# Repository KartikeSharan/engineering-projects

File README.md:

# Engineering Projects: Kartike Sharan

Hardware and software projects from my BEng in Electronics & Electrical Engineering at the University of Glasgow (including an exchange semester at UESTC, Chengdu), my drone society and a drone start-up. Each folder has its own README saying what I did.

## PCB design

| Project | Summary |
|---|---|
| [`atreides-flight-controller`](atreides-flight-controller/) | 6-layer drone flight controller for a start-up; I owned the PCB layout (KiCad) |
| [`gud-drone-devkit`](gud-drone-devkit/) | Solder-free educational drone kit for schools outreach; my electronics design (ESP32-C3, KiCad) |
| [`gud-flight-controller`](gud-flight-controller/) | Society flight controller schematic modelled on the Pixhawk 6 standard (KiCad) |
| [`year1-pcb-design`](year1-pcb-design/) | Electronic dice and logic boards, designed, built and tested (OrCAD, Allegro) |
| [`dp2-orcad-allegro-lab1`](dp2-orcad-allegro-lab1/) | Op-amp board schematic and layout (OrCAD, Allegro) |

## Digital design and HDL

| Project | Summary |
|---|---|
| [`risc16-cpu`](risc16-cpu/) | 16-bit RISC CPU in Verilog, with a review of the submitted design and a revised version with a self-checking testbench run by GitHub Actions |
| [`de2-vhdl-ring-counter`](de2-vhdl-ring-counter/) | Ring counter on a MAX 10 FPGA (Quartus) |
| [`quine-mccluskey`](quine-mccluskey/) | Quine–McCluskey Boolean minimiser in Python with don't-care support |

## Embedded systems

| Project | Summary |
|---|---|
| [`tdp3-line-following-robot`](tdp3-line-following-robot/) | Team robot I lead: register-level C on an Arm Cortex-M0+ with a Python build and flash tool |
| [`stm32-embedded`](stm32-embedded/) | STM32 labs and a cold-chain transport logger (TMP102 over I2C, ADXL345 over SPI) |
| [`rtcs-arm-cortex-m4-labs`](rtcs-arm-cortex-m4-labs/) | Arm Thumb assembly, interrupts and timers on an STM32F407 |

## Analogue, devices and signals

| Project | Summary |
|---|---|
| [`comms-signal-processing-python`](comms-signal-processing-python/) | Sampling, AM and a DFT checked against the FFT, in Python |
| [`tcad-pn-junction`](tcad-pn-junction/) | Silicon p-n junction simulated in Synopsys Sentaurus TCAD |
| [`year1-analogue-labs`](year1-analogue-labs/) | PSpice DC analysis and RC filter labs |

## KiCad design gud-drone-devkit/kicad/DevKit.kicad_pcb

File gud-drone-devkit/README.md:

# Educational drone kit (Glasgow University Drones)

A solder-free, modular drone kit for the society's outreach with secondary schools: pupils assemble and programme it themselves, with JST connectors on the battery and motors and USB-C for power and programming. I proposed the kit and designed its electronics as Head of Electronics.

| | |
|---|---|
| Board | 2-layer, 70.6 x 70.6 mm |
| Main parts | ESP32-C3 module, ICM-42670-P IMU, two DRV8833 dual H-bridges (four motors), TPS63001 buck-boost, BQ24074 charger |
| Power | Buck-boost holds the 3.3 V rail across the LiPo's full range; diode-OR path from USB or battery with reverse-polarity protection |
| Status | ERC/DRC clean, first boards fabricated, not yet assembled |

## Folders

| Folder | Contents |
|---|---|
| `kicad/` | KiCad project, schematic, layout and the custom IMU and connector libraries |
| `manufacturing/` | Gerbers, drill files, BOM and pick-and-place |
| `docs/` | Schematic PDF and the chassis engineering drawing |

The chassis drawing is the mechanical team's; I coordinated PCB size and component positions, including the battery, with them.

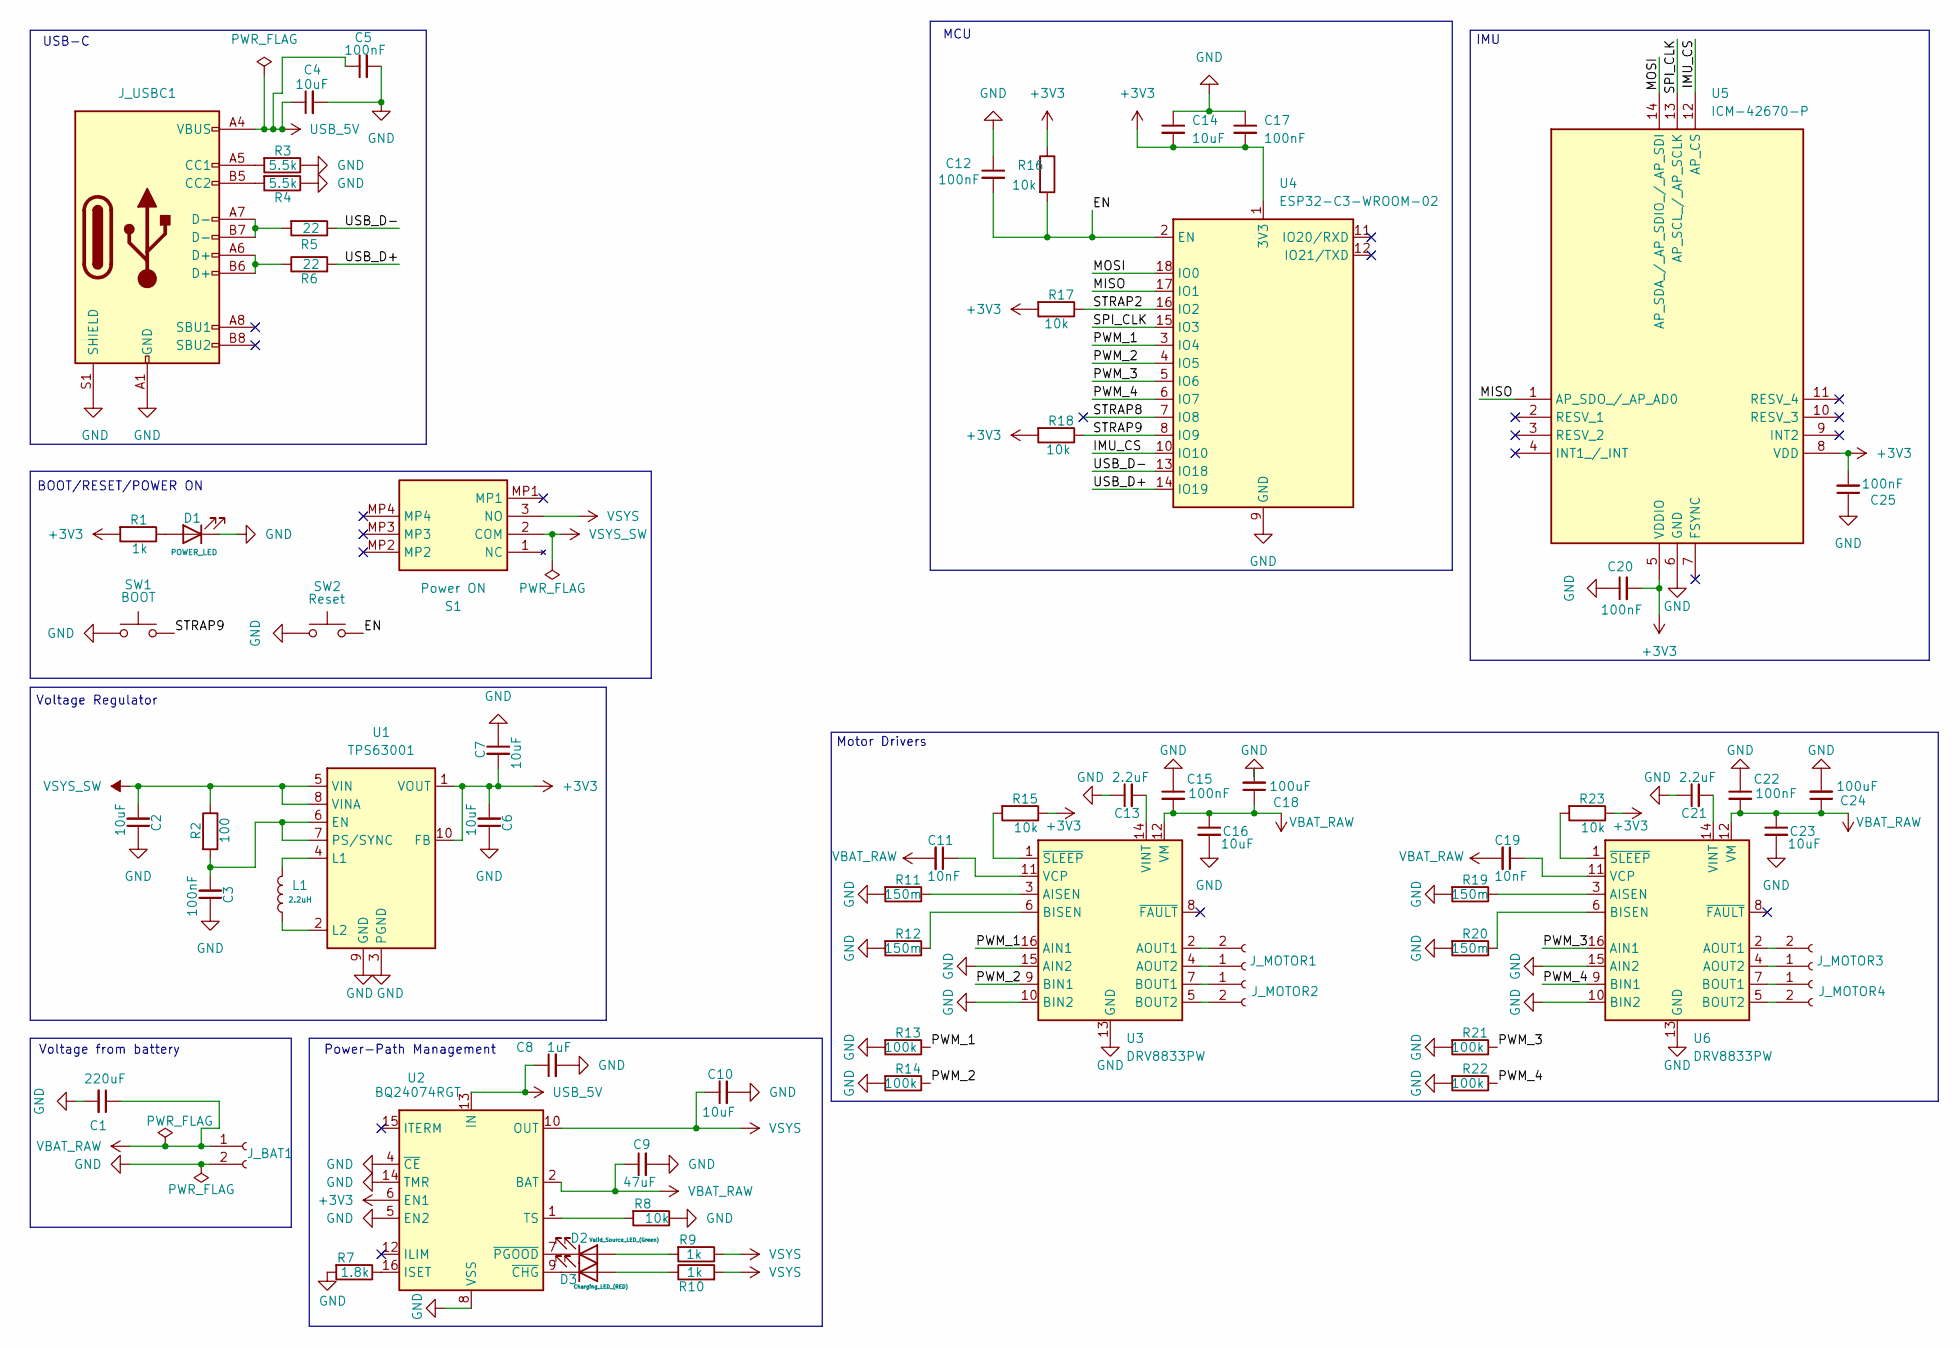
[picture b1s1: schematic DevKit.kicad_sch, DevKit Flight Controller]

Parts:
C1: 220uF; CP_Elec_6.3x5.4
C2, C4, C6, C7, C10, C14, C16, C23: 10uF; C_1206_3216Metric
C3, C5, C12, C15, C17, C20, C22, C25: 100nF; C_0603_1608Metric
C8: 1uF; C_1206_3216Metric
C9: 47uF; C_1206_3216Metric
C11, C19: 10nF; C_0603_1608Metric
C13, C21: 2.2uF; C_0805_2012Metric
C18, C24: 100uF; CP_Elec_6.3x5.4
D1: POWER_LED; LED_0805_2012Metric
D2: Valid_Source_LED_(Green); LED_0805_2012Metric
D3: Charging_LED_(RED); LED_0805_2012Metric
J_BAT1: JST_PH_B2B-PH-K_1x02_P2.00mm_Vertical
J_MOTOR1, J_MOTOR2, J_MOTOR3, J_MOTOR4: JST_GH_BM02B-GHS-TBT_1x02-1MP_P1.25mm_Vertical
J_USBC1: USB_C_Receptacle_GCT_USB4105-xx-A_16P_TopMnt_Horizontal
L1: 2.2uH; L_0805_2012Metric
R1, R9, R10: 1k; R_0603_1608Metric
R2: 100; R_0603_1608Metric
R3, R4: 5.5k; R_0603_1608Metric
R5, R6: 22; R_0603_1608Metric
R7: 1.8k; R_0603_1608Metric
R8, R15, R16, R17, R18, R23: 10k; R_0603_1608Metric
R11, R12, R19, R20: 150m; R_0603_1608Metric
R13, R14, R21, R22: 100k; R_0603_1608Metric
S1: Power ON; PCM12SMTBR; Mouser Part Number 611-PCM12SMTBR
SW1: BOOT; SW_Push_1P1T_NO_CK_KMR2
SW2: Reset; SW_Push_1P1T_NO_CK_KMR2
U1: TPS63001; Texas_DRC0010J_ThermalVias
U2: BQ24074RGT; VQFN-16-1EP_3x3mm_P0.5mm_EP1.6x1.6mm
U3, U6: DRV8833PW; TSSOP-16_4.4x5mm_P0.65mm
U4: ESP32-C3-WROOM-02
U5: ICM-42670-P; ICM42670P; Manufacturer_Part_Number ICM-42670-P; Mouser Part Number 410-ICM-42670-P

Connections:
+3V3: C6.2, C7.2, C14.2, C17.2, C20.2, C25.2, R1.2, R15.1, R16.1, R17.2, R18.2, R23.1, U1.1 (VOUT), U1.10 (FB), U2.6 (EN1), U4.1 (3V3), U5.5 (VDDIO), U5.8 (VDD)
/EN: C12.2, R16.2, SW2.2, U4.2 (EN)
/IMU_CS: U4.10 (IO10), U5.12 (AP_CS)
/MISO: U4.17 (IO1), U5.1 (AP_SDO_/_AP_AD0)
/MOSI: U4.18 (IO0), U5.14 (AP_SDA_/_AP_SDIO_/_AP_SDI)
/PWM_1: R13.1, U3.16 (AIN1), U4.3 (IO4)
/PWM_2: R14.1, U3.9 (BIN1), U4.4 (IO5)
/PWM_3: R21.1, U4.5 (IO6), U6.16 (AIN1)
/PWM_4: R22.1, U4.6 (IO7), U6.9 (BIN1)
/SPI_CLK: U4.15 (IO3), U5.13 (AP_SCL_/_AP_SCLK)
/STRAP2: R17.1, U4.16 (IO2)
/STRAP8: U4.7 (IO8)
/STRAP9: R18.1, SW1.2, U4.8 (IO9)
/USB_D+: R6.2, U4.14 (IO19)
/USB_D-: R5.1, U4.13 (IO18)
GND: C1.2, C2.1, C3.1, C4.2, C5.2, C6.1, C7.1, C8.2, C9.2, C10.2, C12.1, C13.1, C14.1, C15.1, C16.2, C17.1, C18.2, C20.1, C21.1, C22.1, C23.2, C24.2, C25.1, D1.1 (K), J_BAT1.2, J_USBC1.A1 (GND), J_USBC1.A12 (GND), J_USBC1.B1 (GND), J_USBC1.B12 (GND), J_USBC1.S1 (SHIELD), R3.1, R4.1, R7.2, R8.1, R11.2, R12.2, R13.2, R14.2, R19.2, R20.2, R21.2, R22.2, SW1.1, SW2.1, U1.3 (PGND), U1.9 (GND), U1.11 (PGND), U2.4 (~CE), U2.5 (EN2), U2.8 (VSS), U2.14 (TMR), U2.17 (VSS), U3.10 (BIN2), U3.13 (GND), U3.15 (AIN2), U4.9 (GND), U4.19 (GND), U5.6 (GND), U6.10 (BIN2), U6.13 (GND), U6.15 (AIN2)
unnamed: D1.2 (A), R1.1
unnamed: D2.2 (A), R9.2
unnamed: D2.1 (K), U2.7 (~PGOOD)
unnamed: D3.2 (A), R10.1
unnamed: D3.1 (K), U2.9 (~CHG)
unnamed: J_MOTOR1.1, U3.4 (AOUT2)
unnamed: J_MOTOR1.2, U3.2 (AOUT1)
unnamed: J_MOTOR2.1, U3.7 (BOUT1)
unnamed: J_MOTOR2.2, U3.5 (BOUT2)
unnamed: J_MOTOR3.1, U6.4 (AOUT2)
unnamed: J_MOTOR3.2, U6.2 (AOUT1)
unnamed: J_MOTOR4.1, U6.7 (BOUT1)
unnamed: J_MOTOR4.2, U6.5 (BOUT2)
unnamed: J_USBC1.A5 (CC1), R3.2
unnamed: J_USBC1.B5 (CC2), R4.2
unnamed: J_USBC1.A6 (D+), J_USBC1.B6 (D+), R6.1
unnamed: J_USBC1.A7 (D-), J_USBC1.B7 (D-), R5.2
unnamed: C3.2, R2.2, U1.6 (EN), U1.7 (PS/SYNC)
unnamed: L1.2, U1.4 (L1)
unnamed: L1.1, U1.2 (L2)
unnamed: R7.1, U2.16 (ISET)
unnamed: R8.2, U2.1 (TS)
unnamed: R11.1, U3.3 (AISEN)
unnamed: R12.1, U3.6 (BISEN)
unnamed: C11.1, U3.11 (VCP)
unnamed: C13.2, U3.14 (VINT)
unnamed: R15.2, U3.1 (~SLEEP)
unnamed: R19.1, U6.3 (AISEN)
unnamed: R20.1, U6.6 (BISEN)
unnamed: C19.1, U6.11 (VCP)
unnamed: C21.2, U6.14 (VINT)
unnamed: R23.2, U6.1 (~SLEEP)
USB_5V: C4.1, C5.1, C8.1, J_USBC1.A4 (VBUS), J_USBC1.A9 (VBUS), J_USBC1.B4 (VBUS), J_USBC1.B9 (VBUS), U2.13 (IN)
VBAT_RAW: C1.1, C9.1, C11.2, C15.2, C16.1, C18.1, C19.2, C22.2, C23.1, C24.1, J_BAT1.1, U2.2 (BAT), U2.3 (BAT), U3.12 (VM), U6.12 (VM)
VSYS: C10.1, R9.1, R10.2, S1.3 (NO), U2.10 (OUT), U2.11 (OUT)
VSYS_SW: C2.2, R2.1, S1.2 (COM), U1.5 (VIN), U1.8 (VINA)

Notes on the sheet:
MCU
Voltage Regulator
BOOT/RESET/POWER ON
Voltage from battery
USB-C
Power-Path Management
Motor Drivers
IMU

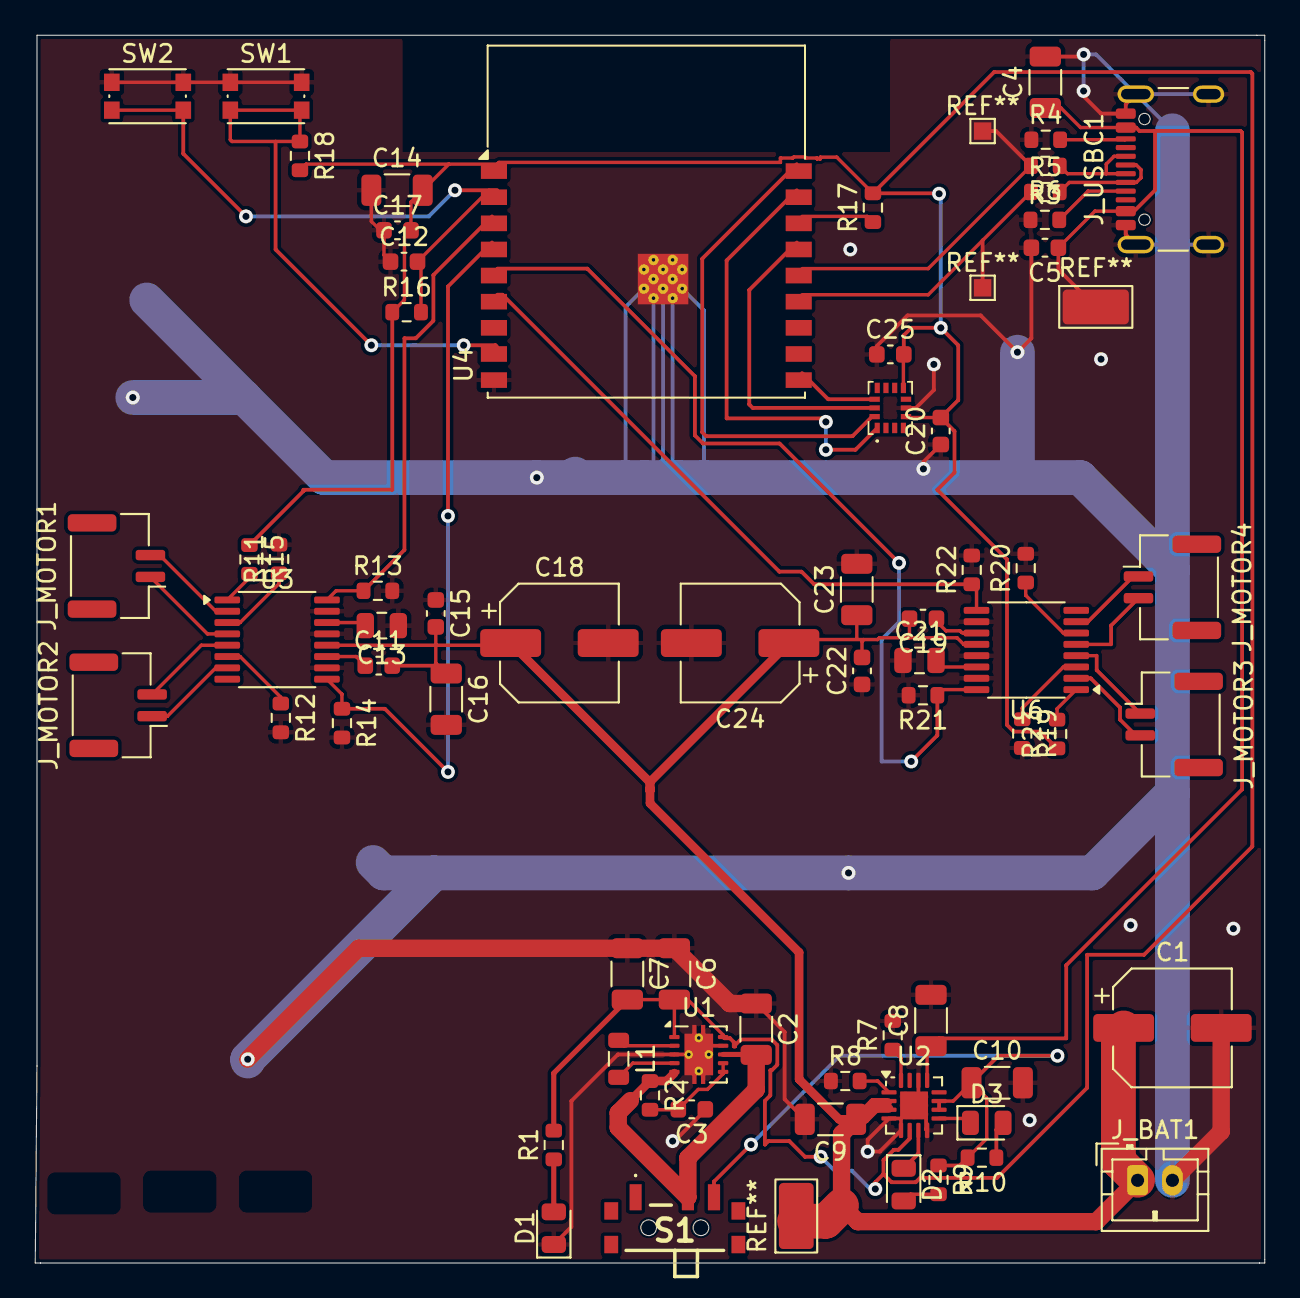
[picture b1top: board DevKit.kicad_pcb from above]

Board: 2 copper layers, 70.6 x 70.5 mm, 67 parts (0 on the bottom side), 51 nets.

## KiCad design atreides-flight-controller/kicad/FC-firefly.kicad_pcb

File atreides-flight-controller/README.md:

# FC-Firefly: drone flight controller PCB (Atreides Industries)

Flight controller board for an early-stage drone start-up, where I worked as a voluntary electronic engineer (Jun to Nov 2025). Added now that the NDA no longer applies.

| | |
|---|---|
| Board | 6-layer, impedance-controlled, 59.6 x 66.6 mm, 2.17 mm thick |
| Parts | 25 BOM lines, 43 placements on the top side |
| Tools | KiCad (schematic, layout, ERC/DRC, Gerber and assembly outputs) |

## My role

I owned the **PCB layout**, working alongside the schematic engineer, who designed the circuit. I checked every footprint against the manufacturers' drawings, cleared ERC and DRC, kept the board's interfaces compatible with the mechanical and electronics engineers, and delivered the manufacture-ready files in `manufacturing/`.

## Folders

| Folder | Contents |
|---|---|
| `kicad/` | KiCad project, schematic and layout, plus the Bosch BMI323 (IMU) and BMM350 (magnetometer) symbol and footprint libraries |
| `manufacturing/gerbers/` | Gerbers, drill files and drill maps as sent to fabrication |
| `manufacturing/assembly/` | BOM and pick-and-place files |

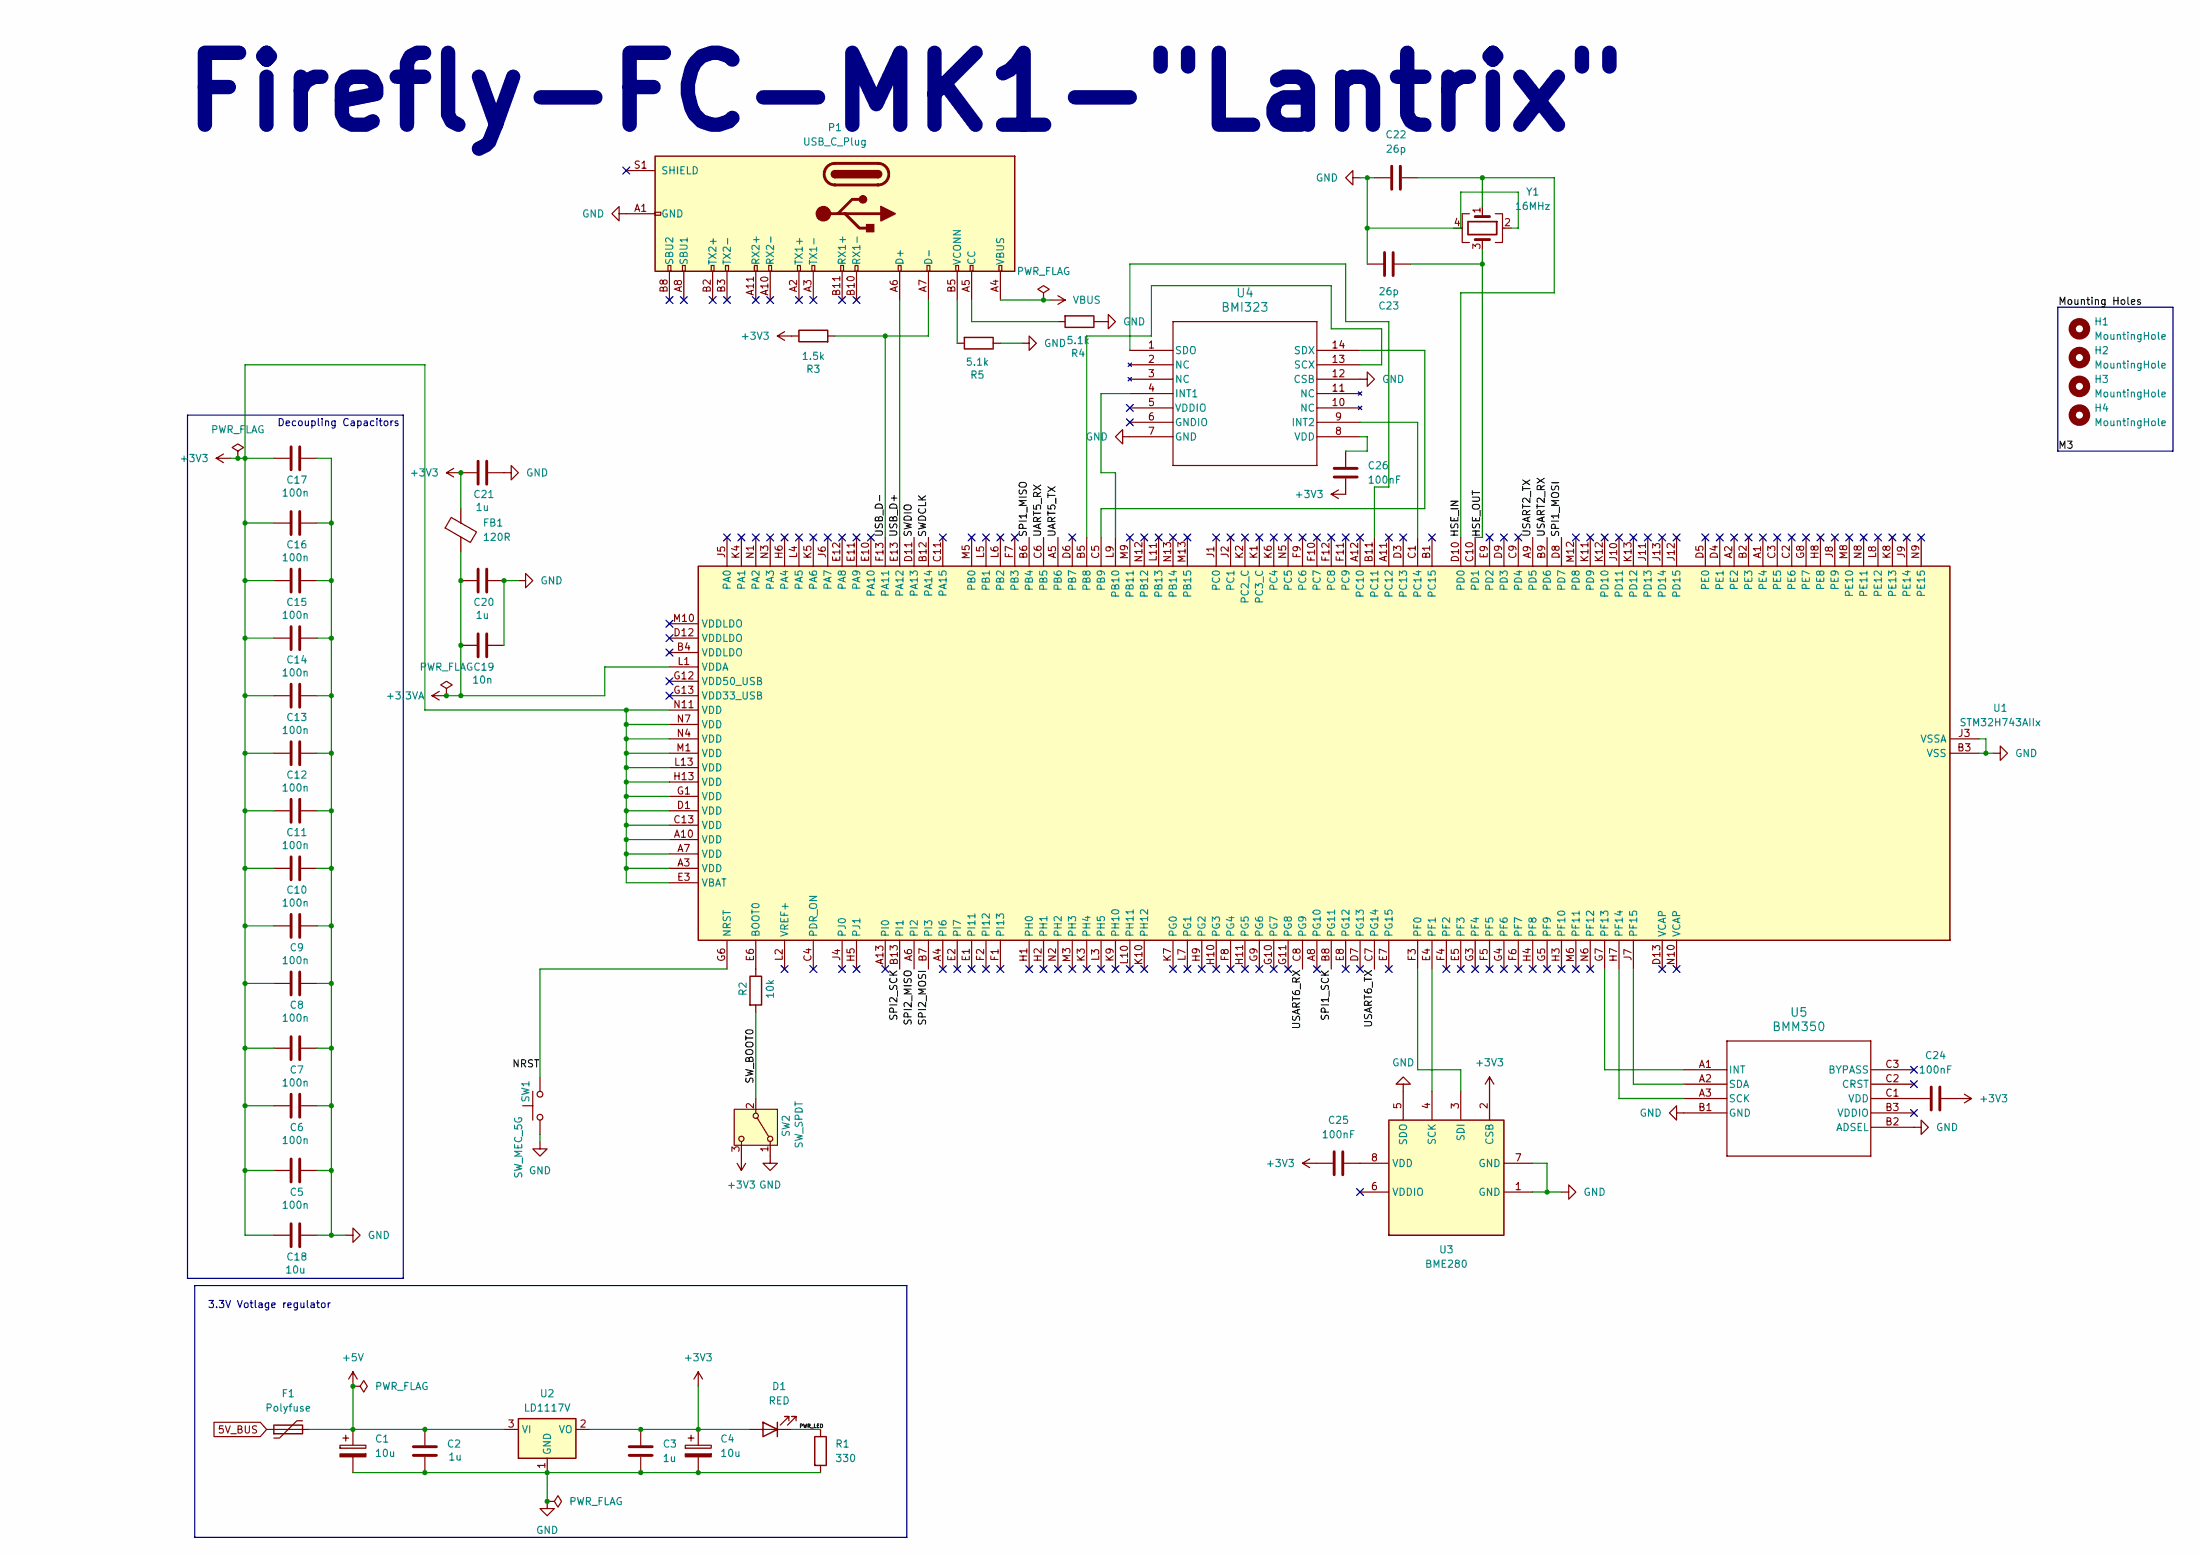
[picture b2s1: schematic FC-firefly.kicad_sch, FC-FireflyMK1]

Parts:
C1, C4: 10u; CP_Elec_3x5.3
C2, C3, C20: 1u; C_0805_2012Metric
C5, C6, C7, C8, C9, C10, C11, C12, C13, C14, C15, C16, C17: 100n; C_0805_2012Metric
C18: 10u; C_0805_2012Metric
C19: 10n; CP_Elec_3x5.3
C21: 1u; CP_Elec_3x5.3
C22, C23: 26p; C_0805_2012Metric
C24, C25, C26: 100nF; C_0805_2012Metric
D1: RED; LED_D5.0mm
F1: Polyfuse; Fuse_1812_4532Metric
FB1: 120R; L_0805_2012Metric
H1, H2, H3, H4: MountingHole; MountingHole_3.2mm_M3
P1: USB_C_Plug; USB_C_Receptacle_HRO_TYPE-C-31-M-12
R1: 330; R_0201_0603Metric_Pad0.64x0.40mm_HandSolder
R2: 10k; R_0201_0603Metric_Pad0.64x0.40mm_HandSolder
R3: 1.5k; R_0201_0603Metric_Pad0.64x0.40mm_HandSolder
R4, R5: 5.1k; R_0201_0603Metric_Pad0.64x0.40mm_HandSolder
SW1: SW_MEC_5G; SW_MEC_5GSH9
SW2: SW_SPDT; SW_SPDT_PCM12
U1: STM32H743AIIx; UFBGA-169_7x7mm_Layout13x13_P0.5mm
U2: LD1117V; TO-220-3_Vertical
U3: BME280; Bosch_LGA-8_2.5x2.5mm_P0.65mm_ClockwisePinNumbering
U4: BMI323; BMI323_BOS
U5: BMM350; BGA9_BMM350_BOS
Y1: 16MHz; Crystal_SMD_3225-4Pin_3.2x2.5mm

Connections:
5V_BUS: F1.1
+3.3VA: C19.1, C20.1, FB1.2, U1.L1 (VDDA)
+3V3: C3.1, C4.1, C5.1, C6.1, C7.1, C8.1, C9.1, C10.1, C11.1, C12.1, C13.1, C14.1, C15.1, C16.1, C17.1, C18.1, C21.1, C24.2, C25.1, C26.1, D1.2 (A), FB1.1, R3.1, SW2.3 (C), U1.A3 (VDD), U1.A7 (VDD), U1.A10 (VDD), U1.C13 (VDD), U1.D1 (VDD), U1.E3 (VBAT), U1.G1 (VDD), U1.H13 (VDD), U1.L13 (VDD), U1.M1 (VDD), U1.N4 (VDD), U1.N7 (VDD), U1.N11 (VDD), U2.2 (VO), U3.2 (CSB)
+5V: C1.1, C2.1, F1.2, U2.3 (VI)
/HSE_IN: C22.2, U1.D10 (PD0), Y1.1
/HSE_OUT: C23.2, U1.C10 (PD1), Y1.3
/NRST: SW1.3 (B), SW1.4 (B), U1.G6 (NRST)
/PWR_LED: D1.1 (K), R1.1
/SPI1_MISO: U1.B6 (PB4)
/SPI1_MOSI: U1.D8 (PD7)
/SPI1_SCK: U1.B8 (PG11)
/SPI2_MISO: U1.A6 (PI2)
/SPI2_MOSI: U1.B7 (PI3)
/SPI2_SCK: U1.B13 (PI1)
/SWDCLK: U1.B12 (PA14)
/SWDIO: U1.D11 (PA13)
/SW_BOOT0: R2.2, SW2.2 (B)
/UART5_RX: U1.C6 (PB5)
/UART5_TX: U1.A5 (PB6)
/USART2_RX: U1.B9 (PD6)
/USART2_TX: U1.A9 (PD5)
/USART6_RX: U1.C8 (PG9)
/USART6_TX: U1.C7 (PG14)
/USB_D+: P1.A6 (D+), U1.E13 (PA12)
/USB_D-: P1.A7 (D-), R3.2, U1.F13 (PA11)
GND: C1.2, C2.2, C3.2, C4.2, C5.2, C6.2, C7.2, C8.2, C9.2, C10.2, C11.2, C12.2, C13.2, C14.2, C15.2, C16.2, C17.2, C18.2, C19.2, C20.2, C21.2, C22.1, C23.1, P1.A1 (GND), P1.A12 (GND), P1.B1 (GND), P1.B12 (GND), R1.2, R4.1, R5.1, SW1.1 (A), SW1.2 (A), SW2.1 (A), U1.B3 (VSS), U1.B10 (VSS), U1.C12 (VSS), U1.D2 (VSS), U1.G2 (VSS), U1.H12 (VSS), U1.J3 (VSSA), U1.L12 (VSS), U1.M2 (VSS), U1.M4 (VSS), U1.M7 (VSS), U1.M11 (VSS), U2.1 (GND), U3.1 (GND), U3.5 (SDO), U3.7 (GND), U4.7 (GND), U4.12 (CSB), U5.B1 (GND), U5.B2 (ADSEL), Y1.2
unnamed: P1.A5 (CC), R4.2
unnamed: P1.B5 (VCONN), R5.2
unnamed: R2.1, U1.E6 (BOOT0)
unnamed: U1.B5 (PB8), U4.13 (SCX)
unnamed: U1.C5 (PB9), U4.14 (SDX)
unnamed: U1.L9 (PB10), U4.4 (INT1)
unnamed: U1.B11 (PC11), U4.1 (SDO)
unnamed: U1.C1 (PC14), U4.9 (INT2)
unnamed: U1.F3 (PF0), U3.3 (SDI)
unnamed: U1.E4 (PF1), U3.4 (SCK)
unnamed: U1.G7 (PF13), U5.A1 (INT)
unnamed: U1.H7 (PF14), U5.A3 (SCK)
unnamed: U1.J7 (PF15), U5.A2 (SDA)
unnamed: C25.2, U3.8 (VDD)
unnamed: C26.2, U4.8 (VDD)
unnamed: C24.1, U5.C1 (VDD)
VBUS: P1.A4 (VBUS), P1.A9 (VBUS), P1.B4 (VBUS), P1.B9 (VBUS)

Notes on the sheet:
3.3V Votlage regulator
Firefly-FC-MK1-"Lantrix"
Decoupling Capacitors

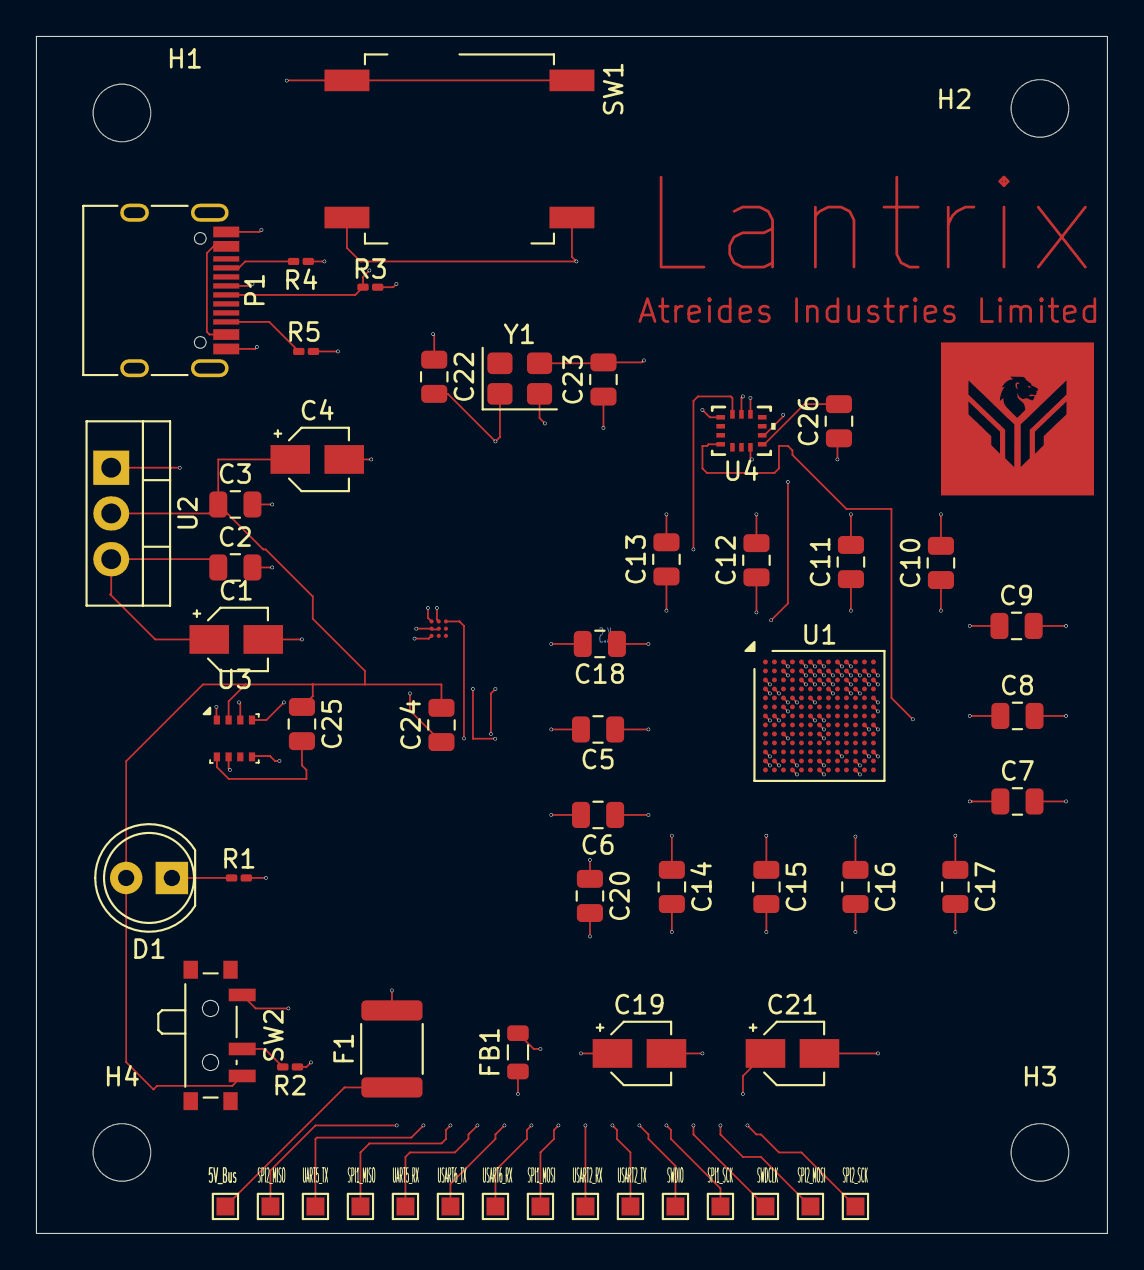
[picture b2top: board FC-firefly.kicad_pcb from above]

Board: 6 copper layers, 59.5 x 66.5 mm, 47 parts (0 on the bottom side), 28 nets.
